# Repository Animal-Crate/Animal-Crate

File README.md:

This project is designed to create an animal noise toy that helps children to learn their animals and their sounds. It is specifically a toy that is meant to better cater to children and individuals with disabilities so that they can learn in a fun and constructive manner with a toy that is appealing and able to meet their needs.

This is a capstone project for the University of Kentucky ECE 490/491 that we are working on as a team. This is the public, open-source repository for this project and all code within this project falls under the provided license in this repository, AGPL-3.0 License. The provided schematics, CAD designs, and other resources are suggestions for recreating this project from home.

---

## Our Goal
The goal of this project is to design a child's toy that makes animal noises that is accessible to a wide-range of audiences, from children with disabilities or impairments to elderly with arthritis and compromised movement.

The provided code will be organized, commented, and user-friendly to allow for the ultimate configuration based on needs and systems. This is our goal as the members working on this project, to ensure that it is robust and well-rounded, allowing those without prior coding knowledge to make changes to suit their needs.

## Prerequisites
Before compiling the programming in this repository, some libraries are necessary for the Arduino IDE. These libraries are not all contained here due to licensing.

The following libraries are required for compiling and uploading to an ESP-32.
- The Animal Toy System utilizes the following libraries:
  - [Arduino LSM6DS3 Library](https://github.com/arduino-libraries/Arduino_LSM6DS3)
  - [DFPlayerMiniFast](https://github.com/PowerBroker2/DFPlayerMini_Fast)
- The Scanner System utilizes the following libraries:
  - [Adafruit ST7735 Library](https://github.com/adafruit/Adafruit-ST7735-Library) (For Testing)
  - [MFRC522](https://github.com/Animal-Crate/Animal-Crate/tree/master/MFRC522)
- The Sound System utilizes the following libraries:
  - [DFRobotDFPlayerMini](https://github.com/DFRobot/DFRobotDFPlayerMini)
  - [ESPSoftwareSerial](https://github.com/plerup/espsoftwareserial/)
- The Video/Algorithm System utilizes the following libraries:
  - [Adafruit GFX Library](https://github.com/adafruit/Adafruit-GFX-Library)
  - [Adafruit ILI9341 Library](https://github.com/adafruit/Adafruit_ILI9341)
  - [Adafruit ImageReader Library](https://github.com/adafruit/Adafruit_ImageReader)
  - [Adafruit SPIFlash](https://github.com/adafruit/Adafruit_SPIFlash)
  - [SdFat](https://github.com/greiman/SdFat)

## Acknowledgements
Please note that the files shown in [MFRC522](https://github.com/Animal-Crate/Animal-Crate/tree/master/_MFRC522) are taken from another repository. These are not licensed under this repository's license, and you can find more information in the README section in that directory.

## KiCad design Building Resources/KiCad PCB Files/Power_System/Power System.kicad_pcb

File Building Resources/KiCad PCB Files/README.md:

The files in this directory are component files for the PCB boards used in this project, created in the [KiCad](https://www.kicad.org/) Software.

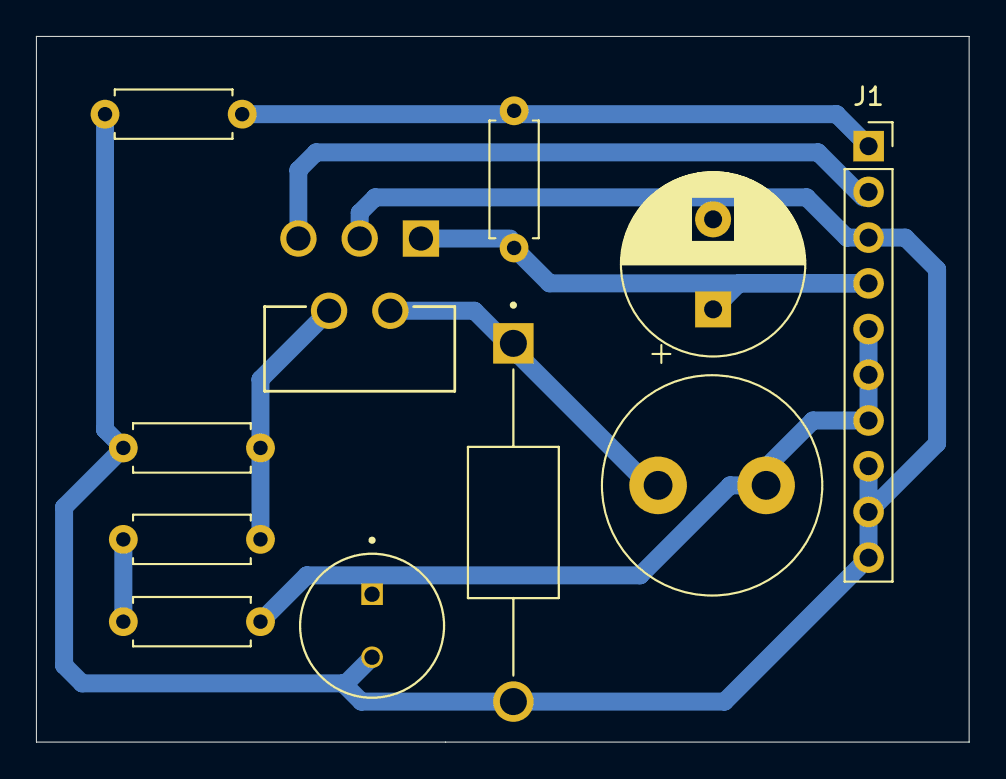
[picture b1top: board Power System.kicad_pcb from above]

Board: 2 copper layers, 51.8 x 39.2 mm, 11 parts (0 on the bottom side), 8 nets.

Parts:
C1: 470 uF; CP_Radial_D10.0mm_P5.00mm
C2: 220uF; 220uFRadialTHCAP
D1: D_Schottky; DIOAD1990W125L840D530
J1: Conn_01x10; PinSocket_1x10_P2.54mm_Vertical
L1: 68mH; L_Radial_D12.0mm_P6.00mm_Murata_1900R
R1: 160k; R_Axial_DIN0207_L6.3mm_D2.5mm_P7.62mm_Horizontal
R2: 82K; R_Axial_DIN0207_L6.3mm_D2.5mm_P7.62mm_Horizontal
R2-1, R2-2: 1.6k; R_Axial_DIN0207_L6.3mm_D2.5mm_P7.62mm_Horizontal
R3: 1k; R_Axial_DIN0207_L6.3mm_D2.5mm_P7.62mm_Horizontal
U1: LM2596T-3.3; TO170P470X1016X2092-5P

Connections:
+6V: C1.1, J1.4, R1.1, U1.1 (VIN)
GNDREF: C1.2, C2.2, D1.2 (A), J1.3, J1.8, J1.9, J1.10, R2.2, R3.1, U1.3 (GND)
unnamed: D1.1 (K), L1.2, U1.2 (OUT)
unnamed: J1.1, R1.2, R2.1
unnamed: J1.2, U1.5 (~ON/OFF)
unnamed: C2.1, J1.5, J1.6, J1.7, L1.1, R2-2.2
unnamed: R2-1.2, R2-2.1
unnamed: R2-1.1, R3.2, U1.4 (FB)

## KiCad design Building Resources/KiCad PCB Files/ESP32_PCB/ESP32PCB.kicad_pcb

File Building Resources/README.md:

The following directory has resources that were used for building or piecing together modules for the project. These correspond to different parts of the main project.

The can include, but are not limited to:
- Pinouts
- CAD Files
- Organization of Parts
- and more.

### Correspondence
Some files here are documentation of the building portion of this project. Some files correspond to testing parts and have remained despite removal of outdated material.
- FP - Pinout.txt: Pinout for testing the display and using it with debugging for the NFC chips.

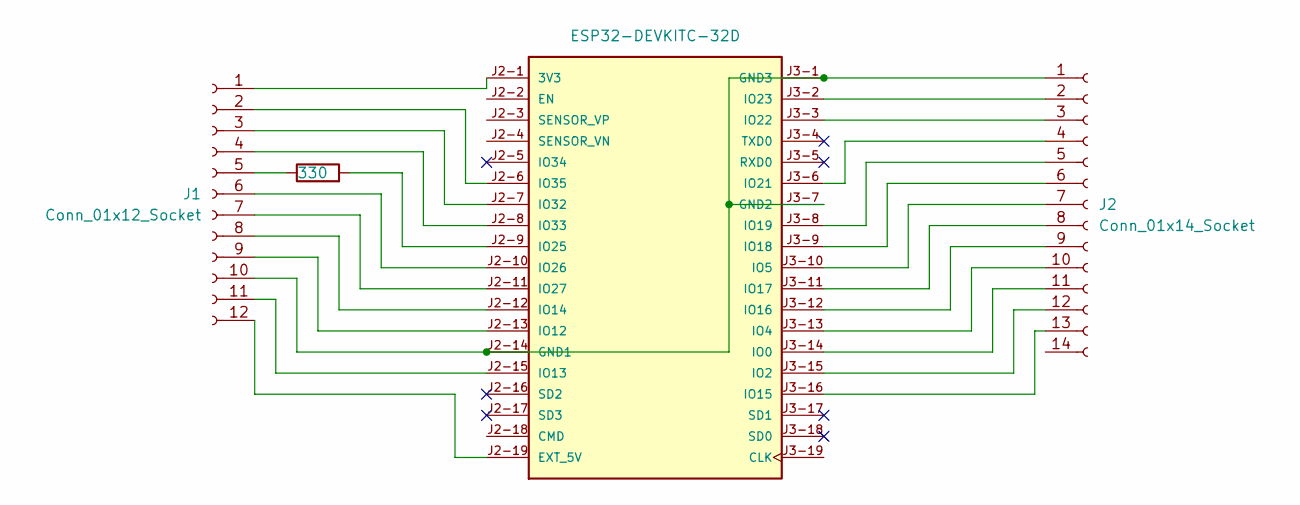
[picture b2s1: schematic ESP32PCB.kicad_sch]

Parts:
J1: Conn_01x12_Socket; PinSocket_1x12_P2.54mm_Vertical
J2: Conn_01x14_Socket; PinSocket_1x14_P2.54mm_Vertical
R1: 330; R_Axial_DIN0207_L6.3mm_D2.5mm_P7.62mm_Horizontal
U1: ESP32-DEVKITC-32D; MODULE_ESP32-DEVKITC-32D; PARTREV V4

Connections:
unnamed: J1.1, U1.J2-1 (3V3)
unnamed: J1.2, U1.J2-6 (IO35)
unnamed: J1.3, U1.J2-7 (IO32)
unnamed: J1.4, U1.J2-8 (IO33)
unnamed: J1.5, R1.1
unnamed: J1.6, U1.J2-10 (IO26)
unnamed: J1.7, U1.J2-11 (IO27)
unnamed: J1.8, U1.J2-12 (IO14)
unnamed: J1.9, U1.J2-13 (IO12)
unnamed: J1.10, J2.1, U1.J2-14 (GND1), U1.J3-1 (GND3), U1.J3-7 (GND2)
unnamed: J1.11, U1.J2-15 (IO13)
unnamed: J1.12, U1.J2-19 (EXT_5V)
unnamed: J2.2, U1.J3-2 (IO23)
unnamed: J2.3, U1.J3-3 (IO22)
unnamed: J2.4, U1.J3-6 (IO21)
unnamed: J2.5, U1.J3-8 (IO19)
unnamed: J2.6, U1.J3-9 (IO18)
unnamed: J2.7, U1.J3-10 (IO5)
unnamed: J2.8, U1.J3-11 (IO17)
unnamed: J2.9, U1.J3-12 (IO16)
unnamed: J2.10, U1.J3-13 (IO4)
unnamed: J2.11, U1.J3-14 (IO0)
unnamed: J2.12, U1.J3-15 (IO2)
unnamed: J2.13, U1.J3-16 (IO15)
unnamed: R1.2, U1.J2-9 (IO25)

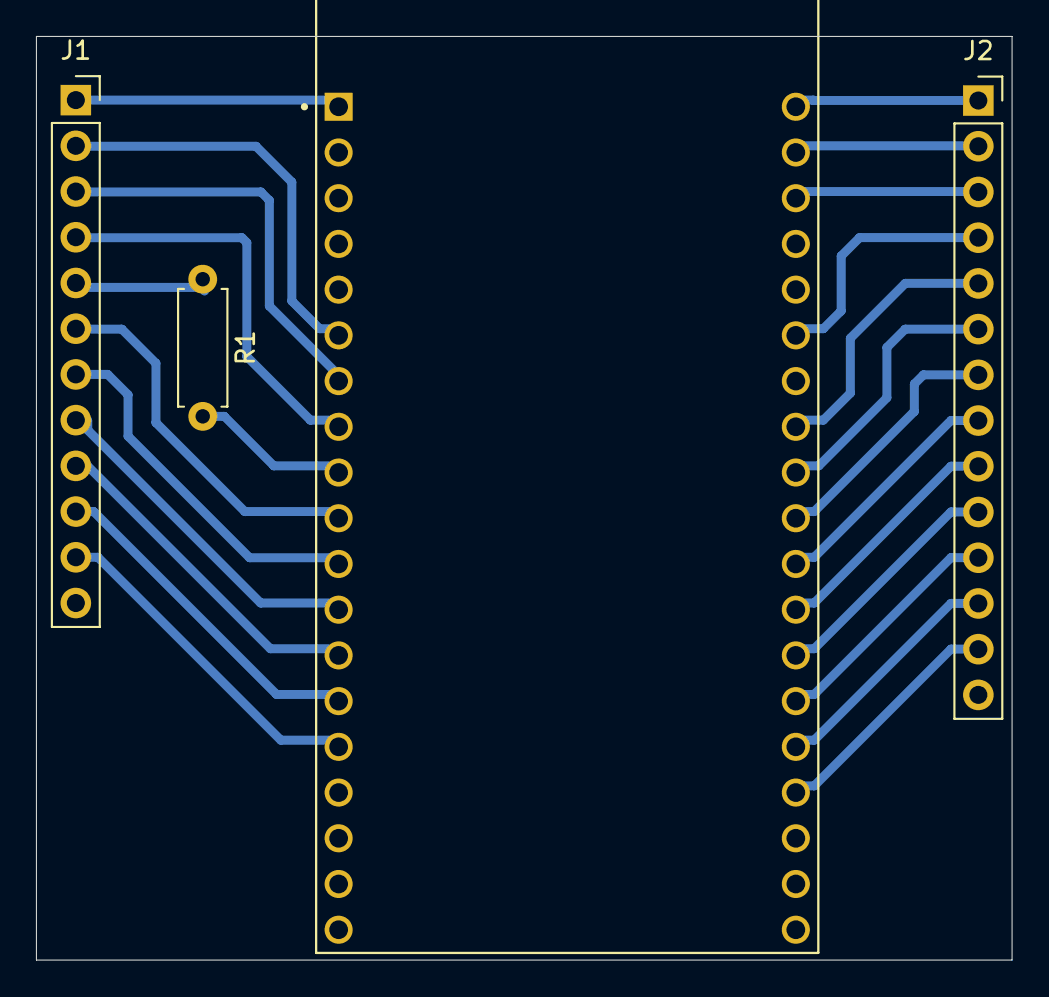
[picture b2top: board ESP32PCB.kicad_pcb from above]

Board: 2 copper layers, 54.2 x 51.3 mm, 4 parts (0 on the bottom side), 25 nets.

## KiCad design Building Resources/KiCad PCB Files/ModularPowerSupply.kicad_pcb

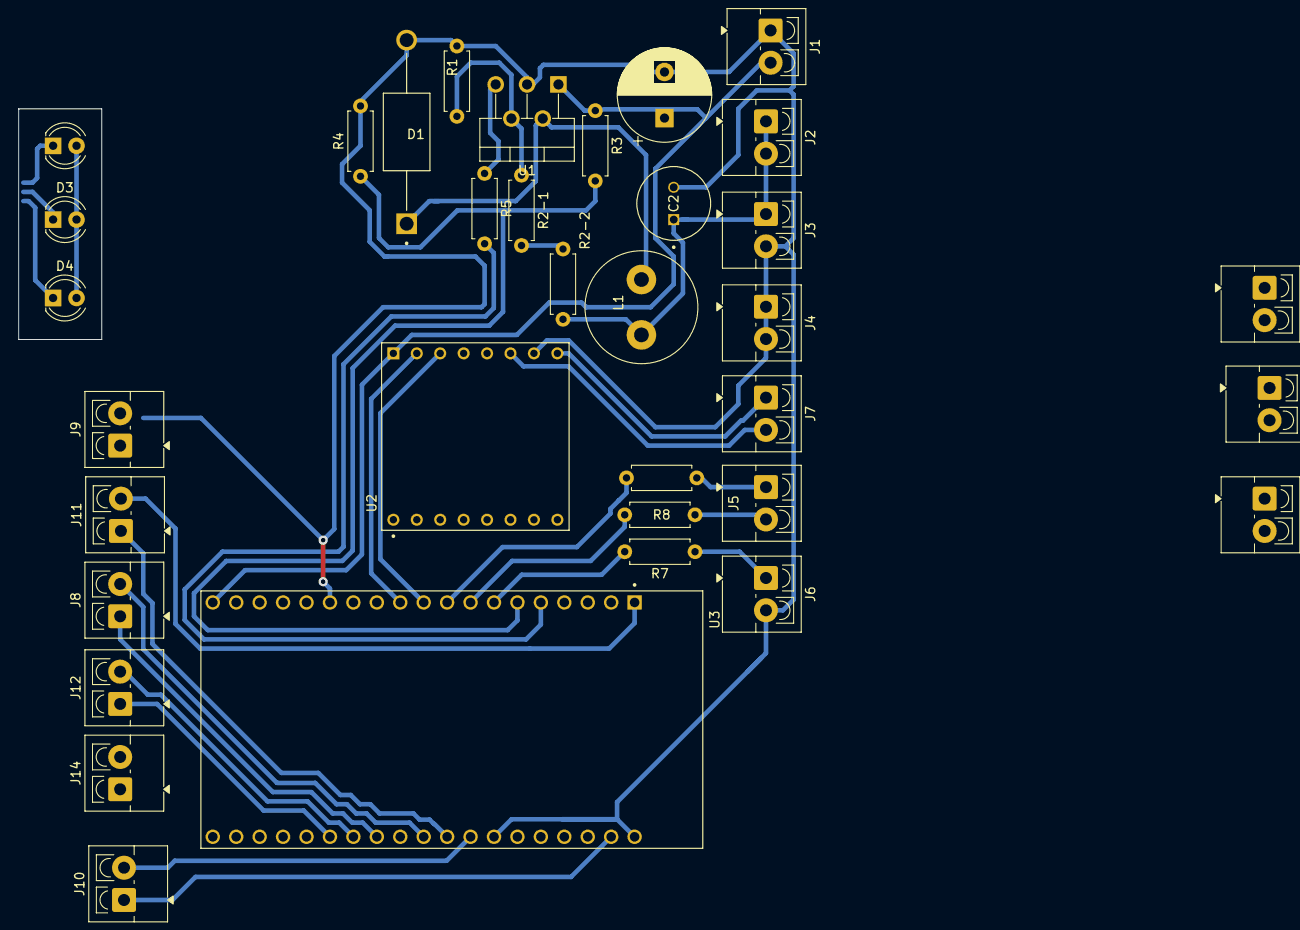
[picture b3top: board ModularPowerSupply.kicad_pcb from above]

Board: 2 copper layers, 35 parts (0 on the bottom side), 36 nets.

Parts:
C2: 220u; 220uFRadialTHCAP
C3: 470 uF; CP_Radial_D10.0mm_P5.00mm
D1: D_Schottky; DIOAD1990W125L840D530
D2: RED; LED_D4.0mm
D3: YELLOW; LED_D4.0mm
D4: GREEN; LED_D4.0mm
J1: BATTERY TERMS; TerminalBlock_4Ucon_1x02_P3.50mm_Vertical
J2: 3.3V; TerminalBlock_4Ucon_1x02_P3.50mm_Vertical
J3: 3.3V AND GND; TerminalBlock_4Ucon_1x02_P3.50mm_Vertical
J4: GND; TerminalBlock_4Ucon_1x02_P3.50mm_Vertical
J5: LED'S; TerminalBlock_4Ucon_1x02_P3.50mm_Vertical
J6: LED'S AND GND; TerminalBlock_4Ucon_1x02_P3.50mm_Vertical
J7: SPEAKER; TerminalBlock_4Ucon_1x02_P3.50mm_Vertical
J8: VOLUME/JOHNS RST; TerminalBlock_4Ucon_1x02_P3.50mm_Vertical
J9: 22/GND; TerminalBlock_4Ucon_1x02_P3.50mm_Vertical
J10: 2319; TerminalBlock_4Ucon_1x02_P3.50mm_Vertical
J11: 3.3/18; TerminalBlock_4Ucon_1x02_P3.50mm_Vertical
J12: 0017; TerminalBlock_4Ucon_1x02_P3.50mm_Vertical
J13: 0504; TerminalBlock_4Ucon_1x02_P3.50mm_Vertical
J14: 0215; TerminalBlock_4Ucon_1x02_P3.50mm_Vertical
J15: 1312; TerminalBlock_4Ucon_1x02_P3.50mm_Vertical
J16: 14; TerminalBlock_4Ucon_1x02_P3.50mm_Vertical
L1: 68m; L_Radial_D12.0mm_P6.00mm_Murata_1900R
R1: 82k; R_Axial_DIN0207_L6.3mm_D2.5mm_P7.62mm_Horizontal
R2-1: 18k; R_Axial_DIN0207_L6.3mm_D2.5mm_P7.62mm_Horizontal
R2-2: 120k; R_Axial_DIN0207_L6.3mm_D2.5mm_P7.62mm_Horizontal
R3: 160k; R_Axial_DIN0207_L6.3mm_D2.5mm_P7.62mm_Horizontal
R4: 82K; R_Axial_DIN0207_L6.3mm_D2.5mm_P7.62mm_Horizontal
R5, R6, R7, R8: 330; R_Axial_DIN0207_L6.3mm_D2.5mm_P7.62mm_Horizontal
U1: LM2596T-3.3; TO-220-5_P3.4x3.7mm_StaggerOdd_Lead3.8mm_Vertical
U2: DFR0299
U3: ESP32-DEVKITC-32D; MODULE_ESP32-DEVKITC-32D

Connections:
+6V: C3.1, J1.2, R3.1, U1.1 (VIN), U2.1 (VCC), U3.J2-19 (EXT_5V)
GNDREF: C2.2, C3.2, D1.2 (A), J1.1, J3.2, J4.1, J4.2, J6.2, J9.2, R1.1, R4.2, U1.3 (GND), U2.7 (GND), U3.J2-14 (GND1), U3.J3-1 (GND3), U3.J3-7 (GND2)
unnamed: D1.1 (K), L1.2, U1.2 (OUT)
unnamed: D2.2 (A), D3.2 (A), D4.2 (A)
unnamed: C2.1, J2.1, J2.2, J3.1, L1.1, R2-2.2
unnamed: J5.1, R8.1
unnamed: J5.2, R6.1
unnamed: J6.1, R7.1
unnamed: J7.1, U2.8 (SPK2)
unnamed: J7.2, U2.6 (SPK1)
unnamed: J8.1, U3.J3-12 (IO16)
unnamed: J8.2, U3.J3-6 (IO21)
unnamed: J9.1, U3.J3-3 (IO22)
unnamed: J10.1, U3.J3-2 (IO23)
unnamed: J10.2, U3.J3-8 (IO19)
unnamed: J11.1, U3.J3-9 (IO18)
unnamed: J11.2, U3.J2-1 (3V3)
unnamed: J12.1, U3.J3-14 (IO0)
unnamed: J12.2, U3.J3-11 (IO17)
unnamed: J13.1, U3.J3-10 (IO5)
unnamed: J13.2, U3.J3-13 (IO4)
unnamed: J14.1, U3.J3-16 (IO15)
unnamed: J14.2, U3.J3-15 (IO2)
unnamed: J15.1, U3.J2-15 (IO13)
unnamed: J15.2, U3.J2-13 (IO12)
unnamed: J16.1, U3.J2-12 (IO14)
unnamed: R2-1.2, R2-2.1
unnamed: R1.2, R2-1.1, U1.4 (FB)
unnamed: R5.1, U1.5 (~ON/OFF)
unnamed: U2.2 (RX), U3.J2-11 (IO27)
unnamed: U2.3 (TX), U3.J2-10 (IO26)
unnamed: R8.2, U3.J2-9 (IO25)
unnamed: R7.2, U3.J2-7 (IO32)
unnamed: R6.2, U3.J2-8 (IO33)
unnamed: R5.2, U3.J2-5 (IO34)
unnamed: R3.2, R4.1, U3.J2-6 (IO35)

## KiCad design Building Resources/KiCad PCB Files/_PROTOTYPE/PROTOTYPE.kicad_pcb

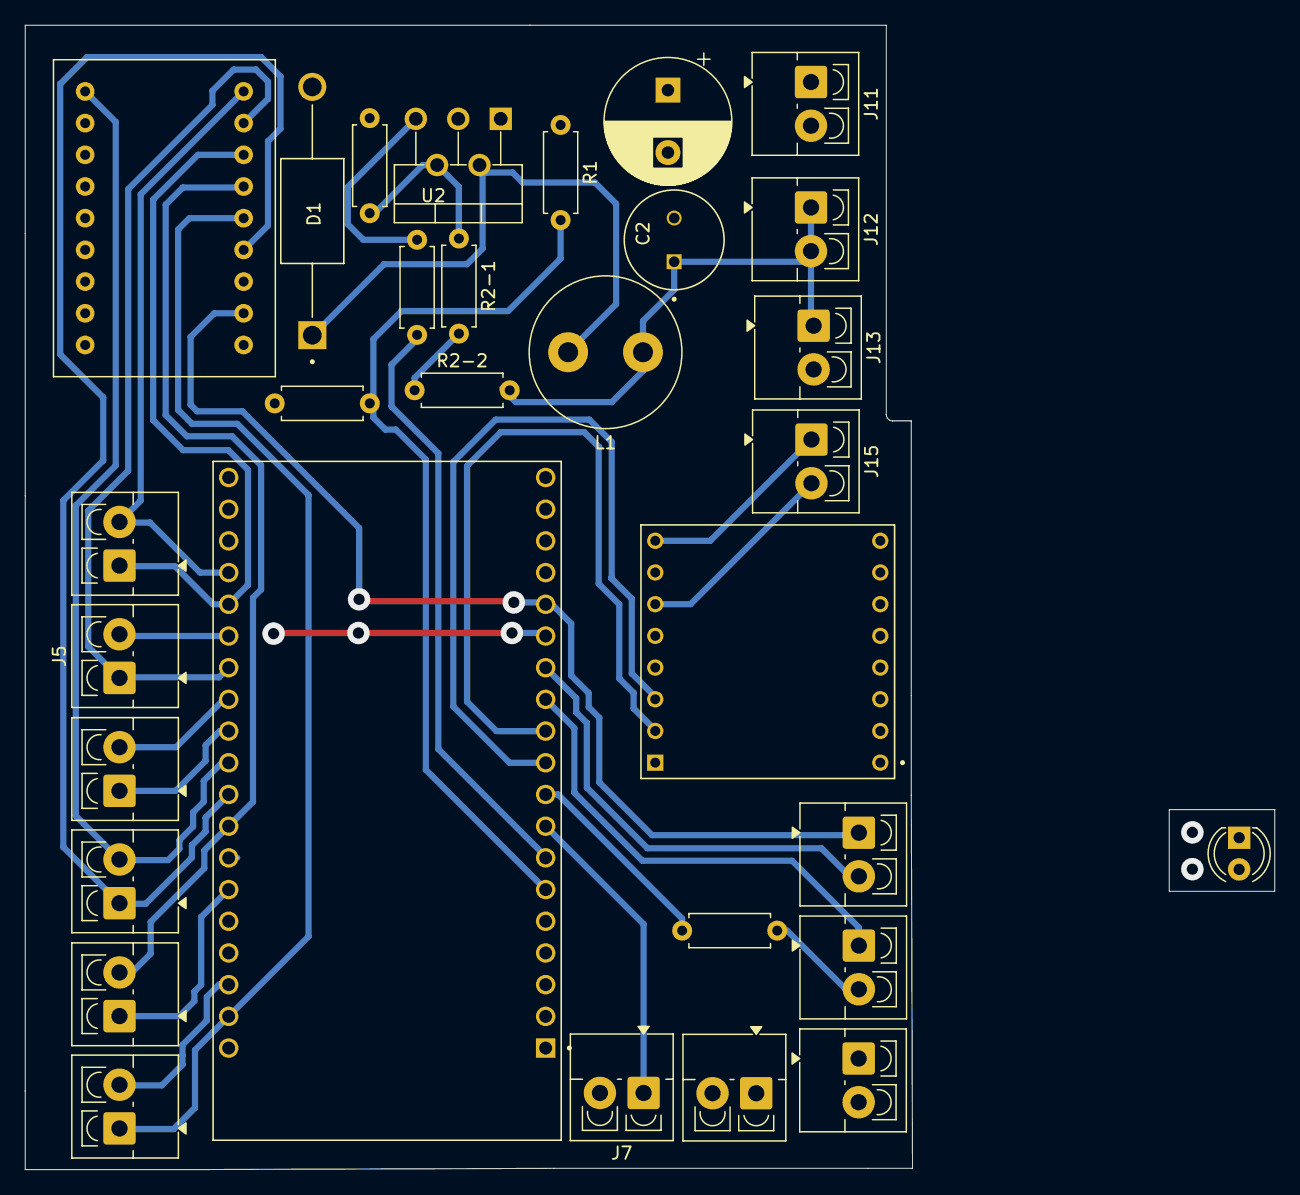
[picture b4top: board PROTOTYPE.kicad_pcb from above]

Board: 2 copper layers, 71.1 x 91.7 mm, 31 parts (0 on the bottom side), 32 nets.

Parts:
C1: 470 uF; CP_Radial_D10.0mm_P5.00mm
C2: 220u; 220uFRadialTHCAP
D1: D_Schottky; DIOAD1990W125L840D530
D2: RED; LED_D4.0mm
EYESPI_18IN_BREAKOUT_BOARD1: DIP-18_500
J1: 2322; TerminalBlock_4Ucon_1x02_P3.50mm_Vertical
J2: 2129; TerminalBlock_4Ucon_1x02_P3.50mm_Vertical
J3: 1805; TerminalBlock_4Ucon_1x02_P3.50mm_Vertical
J4: 1716; TerminalBlock_4Ucon_1x02_P3.50mm_Vertical
J5: 0400; TerminalBlock_4Ucon_1x02_P3.50mm_Vertical
J6: 0215; TerminalBlock_4Ucon_1x02_P3.50mm_Vertical
J7: 33; TerminalBlock_4Ucon_1x02_P3.50mm_Vertical
J8: 2514; TerminalBlock_4Ucon_1x02_P3.50mm_Vertical
J10: 1213; TerminalBlock_4Ucon_1x02_P3.50mm_Vertical
J11: BATTERY TERMS; TerminalBlock_4Ucon_1x02_P3.50mm_Vertical
J12: 3.3V; TerminalBlock_4Ucon_1x02_P3.50mm_Vertical
J13: 3.3V AND GND; TerminalBlock_4Ucon_1x02_P3.50mm_Vertical
J14: GND; TerminalBlock_4Ucon_1x02_P3.50mm_Vertical
J15: SPKR; TerminalBlock_4Ucon_1x02_P3.50mm_Vertical
J16: LED'S AND GND; TerminalBlock_4Ucon_1x02_P3.50mm_Vertical
L1: 68m; L_Radial_D12.0mm_P6.00mm_Murata_1900R
R1: 160k; R_Axial_DIN0207_L6.3mm_D2.5mm_P7.62mm_Horizontal
R2: 82K; R_Axial_DIN0207_L6.3mm_D2.5mm_P7.62mm_Horizontal
R2-1: 18k; R_Axial_DIN0207_L6.3mm_D2.5mm_P7.62mm_Horizontal
R2-2: 120k; R_Axial_DIN0207_L6.3mm_D2.5mm_P7.62mm_Horizontal
R3, R6: 330; R_Axial_DIN0207_L6.3mm_D2.5mm_P7.62mm_Horizontal
R7: 82k; R_Axial_DIN0207_L6.3mm_D2.5mm_P7.62mm_Horizontal
U1: DFR0299
U2: LM2596T-3.3; TO-220-5_P3.4x3.7mm_StaggerOdd_Lead3.8mm_Vertical
U3: ESP32-DEVKITC-32D; MODULE_ESP32-DEVKITC-32D

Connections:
+3.3V: J16.1, U3.J2-1 (3V3)
+6V: C1.1, J11.1, R1.1, U1.1 (VCC), U2.1 (VIN), U3.J2-19 (EXT_5V)
GNDREF: C1.2, C2.2, D1.2 (A), EYESPI_18IN_BREAKOUT_BOARD1.3 (Gnd), J11.2, J13.2, J14.1, J14.2, J16.2, R2.2, R7.1, U1.7 (GND), U2.3 (GND), U3.J2-14 (GND1), U3.J3-1 (GND3), U3.J3-7 (GND2)
unnamed: D1.1 (K), L1.2, U2.2 (OUT)
unnamed: EYESPI_18IN_BREAKOUT_BOARD1.7 (DC), J6.1, U3.J3-15 (IO2)
unnamed: EYESPI_18IN_BREAKOUT_BOARD1.2 (Lite), J10.1, U3.J2-15 (IO13)
unnamed: EYESPI_18IN_BREAKOUT_BOARD1.6 (MISO), J2.2, U3.J3-8 (IO19)
unnamed: EYESPI_18IN_BREAKOUT_BOARD1.5 (MOSI), J1.1, U3.J3-2 (IO23)
unnamed: EYESPI_18IN_BREAKOUT_BOARD1.8 (RST), J5.1, U3.J3-13 (IO4)
unnamed: EYESPI_18IN_BREAKOUT_BOARD1.4 (SCK), J3.1, U3.J3-9 (IO18)
unnamed: EYESPI_18IN_BREAKOUT_BOARD1.10 (SDCS), J3.2, U3.J3-10 (IO5)
unnamed: EYESPI_18IN_BREAKOUT_BOARD1.9 (TCS), J6.2, U3.J3-16 (IO15)
unnamed: C2.1, EYESPI_18IN_BREAKOUT_BOARD1.1 (Vin), J12.1, J12.2, J13.1, L1.1, R2-2.2
unnamed: J1.2, U3.J3-3 (IO22)
unnamed: J2.1, U3.J3-6 (IO21)
unnamed: J4.1, U3.J3-11 (IO17)
unnamed: J4.2, U3.J3-12 (IO16)
unnamed: J5.2, U3.J3-14 (IO0)
unnamed: J7.1, U3.J2-8 (IO33)
unnamed: J8.1, U3.J2-12 (IO14)
unnamed: J8.2, R6.1
unnamed: J10.2, U3.J2-13 (IO12)
unnamed: J15.1, U1.8 (SPK2)
unnamed: J15.2, U1.6 (SPK1)
unnamed: R2-1.2, R2-2.1
unnamed: U1.2 (RX), U3.J2-11 (IO27)
unnamed: U1.3 (TX), U3.J2-10 (IO26)
unnamed: R2-1.1, R7.2, U2.4 (FB)
unnamed: R3.1, U2.5 (~ON/OFF)
unnamed: R6.2, U3.J2-9 (IO25)
unnamed: R3.2, U3.J2-7 (IO32)
unnamed: R1.2, R2.1, U3.J2-6 (IO35)

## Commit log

2025-01-16 Delete GPL License
    This license is the incorrect initial license.
2025-01-16 Port Previous Repository
2025-01-16 Port Previous Repository (#2)
    This ports all previous repository effects.
2025-01-16 Create AnimalCrateTOY.ino (#3)
2025-01-16 Minor change, correcting defintions.
2025-01-16 Move files.
2025-01-16 Update Speaker Toy Test Files (#4)
    * Minor change, correcting defintions.
    * Move files.
2025-01-17 Add Team Logo to README and Update Formatting
    Simply adds the logo to the README and reduces the redundancy by formatting it differently.
2025-01-17 Add Team Logo to README and Update Formatting (#5)
    Simply adds the logo to the README and reduces the redundancy by formatting it differently.
2025-01-21 Add Workflow Initial Setup
2025-01-21 Create sorting file.
2025-01-21 Create sorting file. (#7)
2025-01-21 Add Workflow Initial Setup (#6)
2025-01-21 Add Merge Conflict Checker
    This adds the eps1lon merge conflict labeler.
2025-01-21 Add Merge Conflict Checker (#8)
    This adds the eps1lon merge conflict labeler.
2025-01-21 Add Automated Close from Master/Main
    Adds the actions from superbrothers to automatically close any PR that is made on the master/main branch.
2025-01-21 Add Automated Close from Master/Main (#9)
    Adds the actions from superbrothers to automatically close any PR that is made on the master/main branch.
2025-01-21 Create the PR Template
    This adds the PR template to make it more organized for potential outside users contributing.
2025-01-21 Create the PR Template (#10)
    This adds the PR template to make it more organized for potential outside users contributing.
2025-01-21 Delete the AnimalCrateTOY File
    This file no longer is used in this repository and does not work with the hardware for the individual toys. We're removing this for now to prevent any conflicts in the future.
2025-01-21 Uploading Feedback code
    Main menu
2025-01-21 Delete the AnimalCrateTOY File (#11)
    This file no longer is used in this repository and does not work with the hardware for the individual toys. We're removing this for now to prevent any conflicts in the future.
2025-01-21 Uploading Feedback code (#12)
    Main menu
2025-01-21 Move to a dedicated folder for Arduino Formatting.
2025-01-21 Move to a dedicated folder for Arduino Formatting. (#13)
2025-01-22 Create AnimalToy1.0.ino
    This is the first edition of the code before I added the sound files in that will upload directly to the Arduino for the Animal sounds. Currently this code only produces a beep when the device is sha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
2025-01-22 Create AnimalToy1.0.ino (#14)
    This is the first edition of the code before I added the sound files in that will upload directly to the Arduino for the Animal sounds. Currently this code only produces a beep when the device is sha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
2025-01-22 Add Arduino Files to Labeler
    This adds the .ino extension to the labeler so it doesn't forget to flag Arduino changes.
2025-01-22 Add Arduino Files to Labeler (#15)
    This adds the .ino extension to the labeler so it doesn't forget to flag Arduino changes.
2025-02-19 Create AnimalToy2.0
    This version of the code shows the changes made to initialize the DF Player Mini with the sound file that is on there for the animal after the device is shaken. As well as the circuit now includes a 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
2025-02-19 Create AnimalToy2.0 (#16)
    This version of the code shows the changes made to initialize the DF Player Mini with the sound file that is on there for the animal after the device is shaken. As well as the circuit now includes a 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
2025-02-19 Create AnimalToy2.1(T-Shoot)
    This edition of the code has trouble shooting code in it and may be of assistance if having issues with the DF Player Mini, This code should run Identical to the previous patch.
    NOTE: The timing for the Transistor may not be what is needed and may require editing as needed depending on the length of the Animal sound being played.
2025-02-20 Fix AnimalToy code.
    This fixes the structure and turns it into a .ino file so that it follows the required naming scheme that Arduino uses.
2025-02-20 Fix AnimalToy code. (#18)
    This fixes the structure and turns it into a .ino file so that it follows the required naming scheme that Arduino uses.
2025-02-20 Rename AnimalToy2.1(T-Shoot) to AnimalToy2.1(T-Shoot).ino
    This will fix the naming issue before submitting this PR.
2025-02-20 Create AnimalToy2.1(T-Shoot) (#17)
    * Create AnimalToy2.1(T-Shoot)
    This edition of the code has trouble shooting code in it and may be of assistance if having issues with the DF Player Mini, This code should run Identical to the previous patch.
    NOTE: The timing for the Transistor may not be what is needed and may require editing as needed depending on the length of the Animal sound being played.
    * Rename AnimalToy2.1(T-Shoot) to AnimalToy2.1(T-Shoot).ino
    This will fix the naming issue before submitting this PR.
    ---------
2025-03-11 Create SoundWithbuttons.ino
    Plays sound with a push button and changes volume also.
2025-03-11 Create SoundWithbuttons.ino (#19)
    Plays sound with a push button and changes volume also.
2025-03-14 Add files via upload (#21)
2025-03-25 Create Sound Directory
2025-03-25 Create Sound Directory (#22)
2025-03-25 Add files via upload (#23)
2025-03-25 Update SoundWithbuttons.ino
    Changed the volume increments to 3 and default volume to 15
2025-03-25 Update SoundWithbuttons.ino (#24)
    Changed the volume increments to 3 and default volume to 15
2025-03-25 Change Directories and Delete Old Versions
2025-03-25 Change Naming Scheme & Delete Outdated Versions (#25)
    * Change Directories and Delete Old Versions
    * Change the Feedback Code to be more intuitive.
2025-03-25 Change the Feedback Code to be more intuitive.
2025-03-25 Update the .gitignore file.
2025-03-25 Update the .gitignore file. (#26)
2025-03-25 Update Animal Sounds README
2025-03-25 Update README for Animal Sounds again.
2025-03-25 Update main README.
2025-03-25 Fix Le Typo
2025-03-25 Update READMEs. (#27)
    * Update Animal Sounds README
    * Update README for Animal Sounds again.
    * Update main README.
    * Fix Le Typo
2025-03-25 Add Building Resources and README for it.
2025-03-25 Add Building Resources and README for it. (#28)
2025-03-27 Change some comments and prepare for further integration.
2025-03-27 Adding Kicad PCB and Schematic Files
2025-03-27 Sort in Directory 1
2025-03-27 Sort in Directory 2
2025-03-27 Sort in Directory 3
2025-03-27 Update Labeler for PCB Files
    Updates the labeler auto-check for the PCB Files.
2025-03-27 Update Labeler for PCB Files (#31)
    Updates the labeler auto-check for the PCB Files.
2025-03-27 Change 1 Again
2025-03-27 Change 2 Again
2025-03-27 Change 3 Again
2025-03-27 Adding Kicad PCB and Schematic Files (#29)
    * Adding Kicad PCB and Schematic Files
    * Sort in Directory 1
    * Sort in Directory 2
    * Sort in Directory 3
    * Change 1 Again
    * Change 2 Again
2025-03-27 Initial Audio Integration (#30)
    * Initial Commit
    * Change some comments and prepare for further integration.
2025-03-27 Add More Libraries to README (#32)
    * Update README.md
    * Update README.md
2025-04-01 Initial commit, removing display and setting up hardware interrupts. This has problems, do not make a PR without checking this over.
2025-04-03 Sets up the rest of the interrupts with a play by button sound system.
2025-04-03 Interrupts Setup & Remove Display in Audio/Scanner Integration (#33)
    * Initial commit, removing display and setting up hardware interrupts. This has problems, do not make a PR without checking this over.
    * Sets up the rest of the interrupts with a play by button sound system.
2025-04-03 Initial setup.
2025-04-04 Update AlgorithmButtonFeedbackCode.ino (#35)
2025-04-05 Finsih integration.
2025-04-05 Finish Audio & Scanner Integration (#36)
    * Initial setup.
    * Finsih integration.
2025-04-05 Upload new KiCad Files.
2025-04-05 Upload new KiCad Files. (#37)
2025-04-05 Update Organization and Provide README for KiCad Building Resources.
2025-04-05 Provide README
2025-04-05 Update KiCad Organization and README (#38)
    * Update Organization and Provide README for KiCad Building Resources.
    * Provide README
2025-04-05 Fix PURPOSE section.
2025-04-05 Update more Libraries
    Adds more libraries to the README for necessary compilation.
2025-04-05 Update more Libraries (#39)
    Adds more libraries to the README for necessary compilation.
2025-04-05 More Touchups
2025-04-05 Initial Branch
2025-04-05 Additional Additions.
2025-04-05 Fix one noticed mistake. Change to volatile due to ISR.
2025-04-08 Finish Integration. Tests Remain.
2025-04-08 More touchups.
2025-04-08 Fix ISR.
2025-04-08 Audio/Video & Scanner Integration (#41)
    * Initial Branch
    * Additional Additions.
    * Fix one noticed mistake. Change to volatile due to ISR.
    * Finish Integration. Tests Remain.
    * Fix ISR.
2025-04-08 Integration Program TouchUps (#40)
    * Fix PURPOSE section.
    * More Touchups
    * More touchups.
2025-04-10 Update AlgorithmButtonFeedbackCode.ino (#42)
2025-04-10 Massive update fix for current play board. Fixes screen issues as well.
2025-04-10 Massive update fix for current play board. Fixes screen issues as well. (#43)
2025-04-11 Fix BCK_LIGHT Pin and Setup (#44)
    Fixes setup for Arduino IDE.
2025-04-11 Update README with Purpose and Goal. Update Team-Logo.
2025-04-11 Update Description and Logo (#45)
2025-04-11 Add README to Integration Tests.
2025-04-11 Add README to Integration Tests (#46)
2025-04-11 Combine Directories
2025-04-11 Rename Files to be more appropriate and alike.
2025-04-12 Add README
2025-04-12 Add README and update MFRC directory
2025-04-12 Update Subsystem Directories & Add README (#47)
    * Combine Directories
    * Rename Files to be more appropriate and alike.
    * Add README
2025-04-12 Update Prerequisites and MFRC Directory (#48)
2025-04-12 Fix Bad Directory
2025-04-12 Fix Bad Directory (#49)
2025-04-12 Update PCB Auto-Labeler
2025-04-12 Update PCB Files
2025-04-12 Add a Drivers directory and add the other files to the Power_Supply.
2025-04-12 Add the other PCB boards and the PROTOTYPE board.
2025-04-12 Update the initial README.
2025-04-12 Update PCB Auto-Labeler (#50)
    * Update PCB Auto-Labeler
    * Update labeler.yml
2025-04-12 Add Issue Templates
    This adds issue templates for future use. I just wanted to add them in my free time so GitHub stops suggesting it. :)
2025-04-12 Add Issue Templates (#52)
2025-04-12 Add the first Release Program w/ README
2025-04-12 Fix gameMode() in AV_ScannerIntegration
2025-04-12 Update the KiCad Files for Split Design (#51)
2025-04-14 Fix gameMode() in AV_ScannerIntegration (#53)
2025-04-14 Add Control Program and Release Programs Directory w/ README (#54)
2025-04-16 Fix GameMode Indexing Errors
2025-04-16 Add Control_Program with no Serial
2025-04-17 Fix GameMode() Indexing Errors in Integration & Release (#55)
2025-04-17 Add Control_Program (#56)
2025-04-23 Add Citation for Referencing
    This just adds a citation file for referencing this repository instead of jumping through hoops to reference using an external website.
2025-04-23 Add Citation for Referencing (#57)
2025-04-24 Update some logging and delays.
2025-04-24 Update KiCad Files
2025-04-26 Indexing Fix
2025-04-26 Fix rest of index, add sound cue for volume buttons, fix repeat triggers on menu.
2025-04-26 More updates, finally.
2025-04-26 Update Serial Debug and Delays in Release Programs (#58)
2025-04-26 Update KiCad Files (#59)
2025-04-26 Fix Indexing, Screen Repeats, Spacing on Menu, and Add Volume Cue (#60)
2025-04-26 Add Charge_Detection and add entry in README.md
2025-04-26 Add Charge Detection to Releases
2025-04-26 Update Voltage Thresholds
2025-04-26 Update LED Levels
2025-04-26 Add Charge_Detection Subsystem (#61)
2025-04-26 Add Charge Detection to Releases (#62)
2025-05-05 Add CAD Designs
2025-05-05 Add CAD to Labeler
2025-05-05 Add CAD to Labeler (#63)
2025-05-05 Finish Building Resources - Adding CAD Designs (#64)
